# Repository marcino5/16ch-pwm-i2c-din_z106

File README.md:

# PCB 16xPWM i2c
This repository contains KiCAD files. This is an expansion module containing 16 PWM 12-24V outputs. The circuit consists of 16 N-Channel MOSFETs with a load capacity of 10A per channel controlled by a 12-bit LED controller PCA9685PW with an I2C interface. The circuit is not adapted to the maximum current, and for higher currents it is necessary to tin the exposed plus path. In my home configuration with ESPHome it works with 4 meter LED strips per channel and I did not observe any heating of the paths.

The PCB is designed to fit in a commonly available DIN rail housing.

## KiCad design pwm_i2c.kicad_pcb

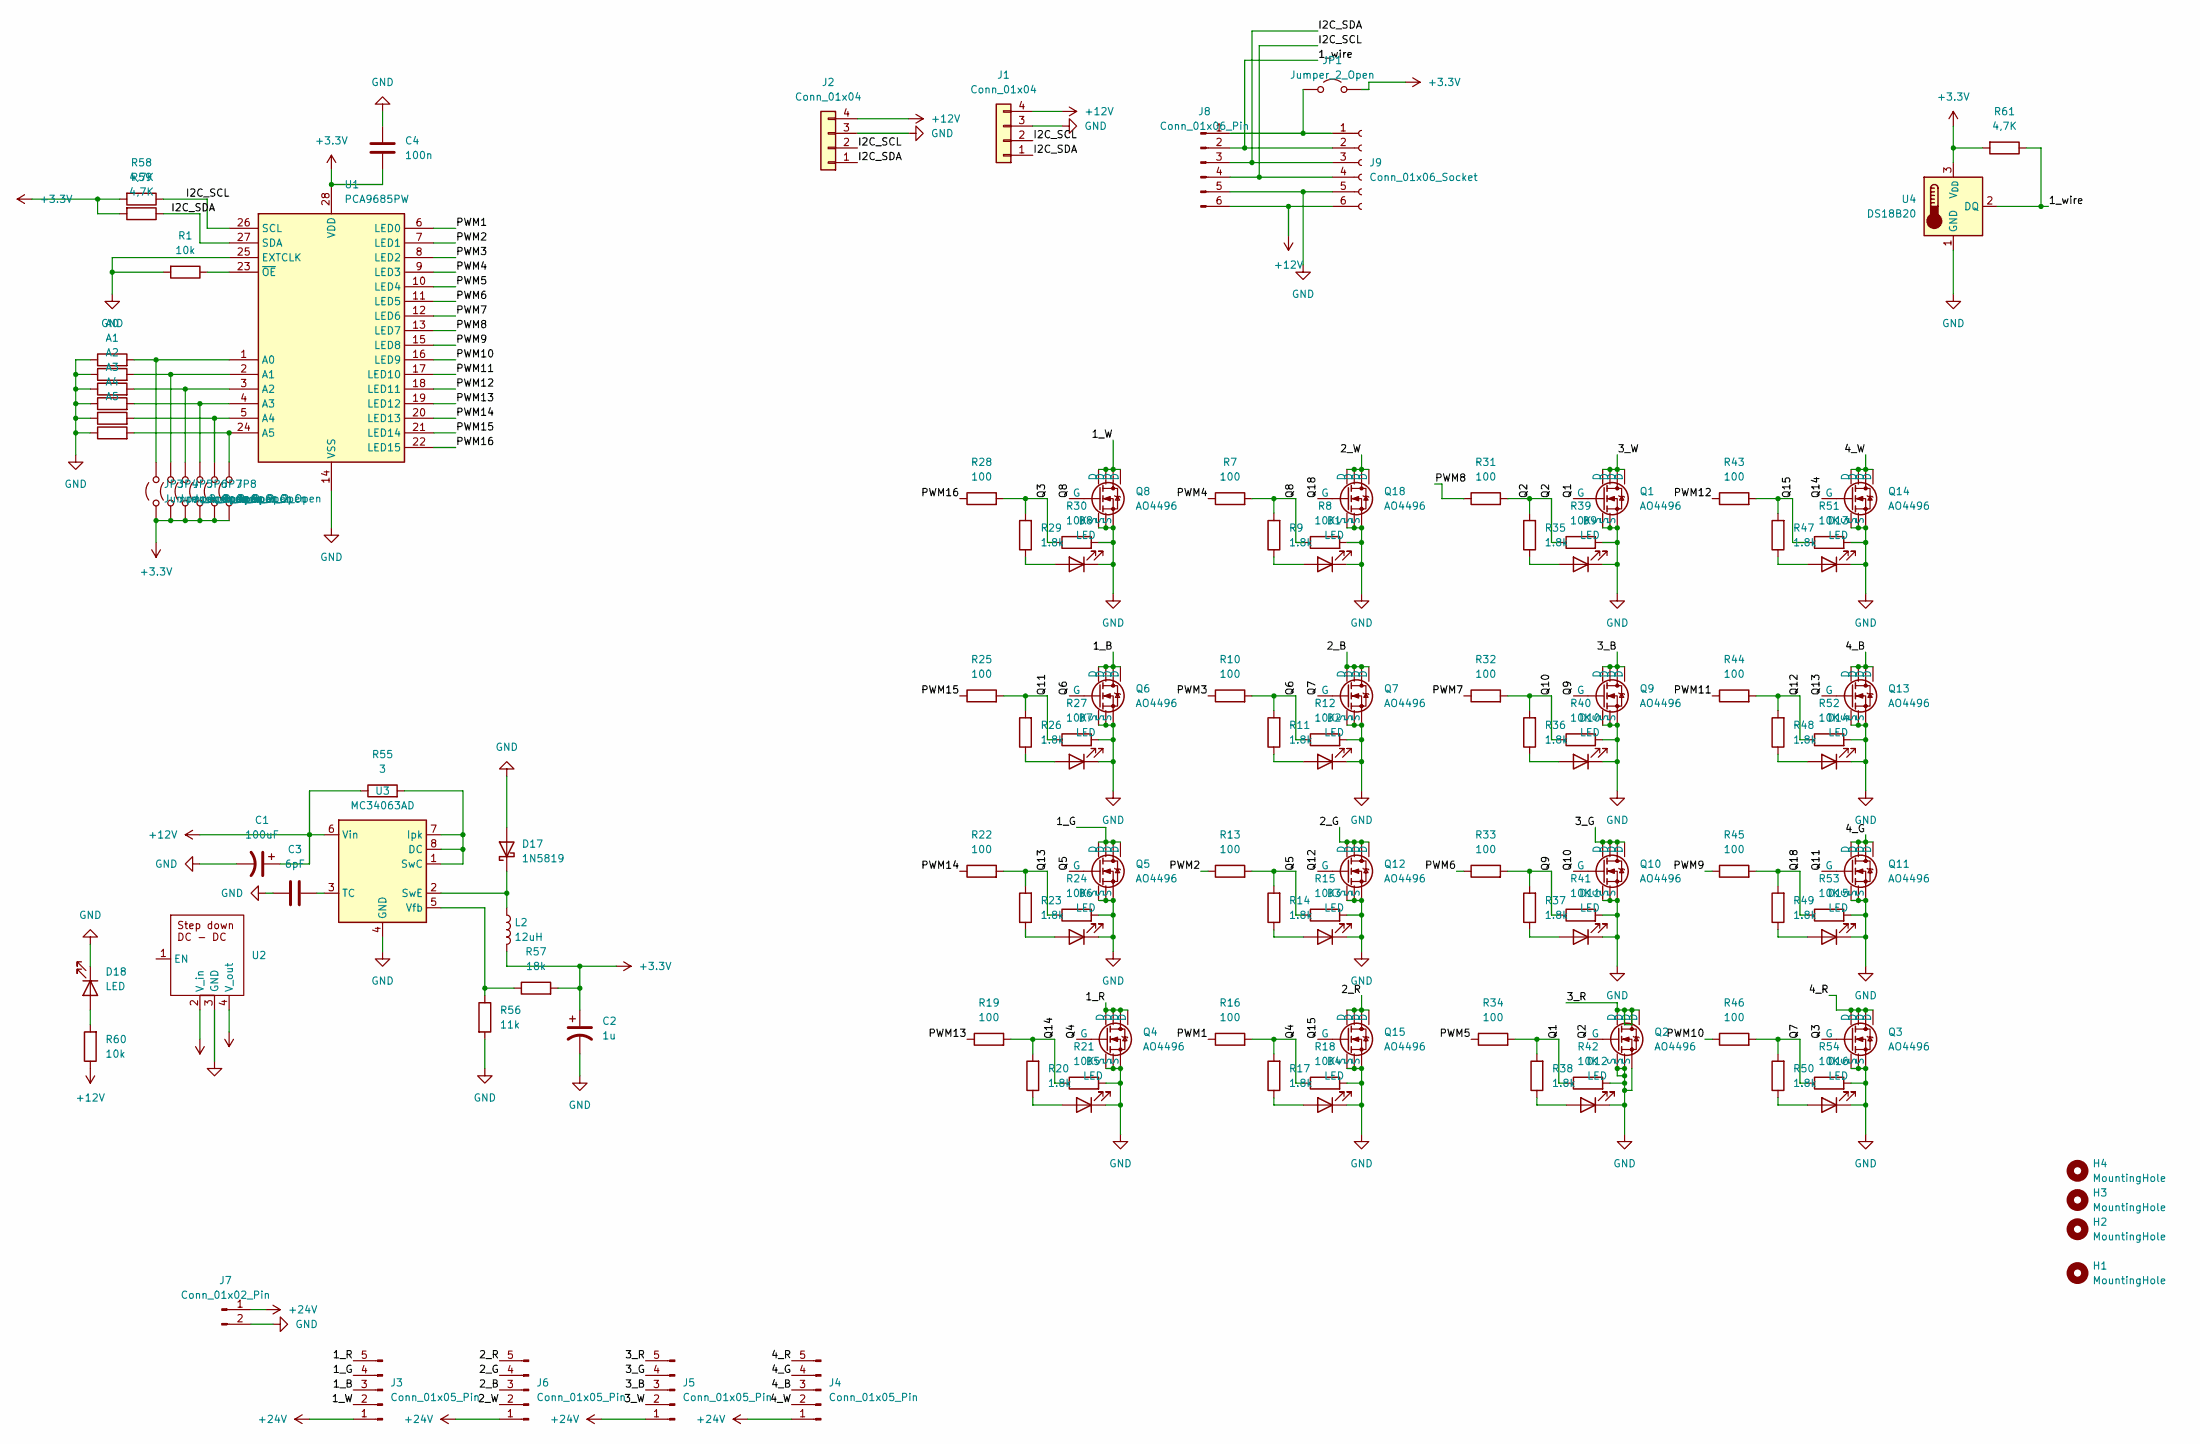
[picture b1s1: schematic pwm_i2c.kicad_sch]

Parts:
A0, A1, A2, A3, A4, A5: R_1206_3216Metric
C1: 100uF; CP_Elec_8x6.9
C2: 1u; CP_Elec_5x5.3
C3: 6pF; CP_EIA-3528-15_AVX-H
C4: 100n; C_1206_3216Metric_Pad1.33x1.80mm_HandSolder
D1, D2, D3, D4, D5, D6, D7, D8, D9, D10, D11, D12, D13, D14, D15, D16: LED; LED_1206_3216Metric
D17: 1N5819; D_MELF
D18: LED; LED_1206_3216Metric_Pad1.42x1.75mm_HandSolder
H1, H2, H3, H4: MountingHole; MountingHole_3.2mm_M3_ISO7380
J1, J2: Conn_01x04; NS-Tech_Grove_1x04_P2mm_Vertical
J3, J4, J5, J6: Conn_01x05_Pin; PhoenixContact_MC_1,5_5-G-3.81_1x05_P3.81mm_Horizontal
J7: Conn_01x02_Pin; PhoenixContact_MC_1,5_2-G-3.81_1x02_P3.81mm_Horizontal
J8: Conn_01x06_Pin; PinHeader_1x06_P2.54mm_Horizontal
J9: Conn_01x06_Socket; PinHeader_1x06_P2.54mm_Horizontal
JP1, JP3, JP4, JP5, JP6, JP7, JP8: Jumper_2_Open; SolderJumper-2_P1.3mm_Open_TrianglePad1.0x1.5mm
L2: 12uH; L_Changjiang_FNR4010S
Q1, Q2, Q3, Q4, Q5, Q6, Q7, Q8, Q9, Q10, Q11, Q12, Q13, Q14, Q15, Q18: AO4496; SO-8_5.3x6.2mm_P1.27mm
R1, R60: 10k; R_1206_3216Metric
R7, R10, R13, R16, R19, R22, R25, R28, R31, R32, R33, R34, R43, R44, R45, R46: 100; R_1206_3216Metric
R8, R12, R15, R18, R21, R24, R27, R30, R39, R40, R41, R42, R51, R52, R53, R54: 10K; R_1206_3216Metric
R9, R11, R14, R17, R20, R23, R29, R35, R36, R37, R38, R47, R48, R49, R50: 1.8k; R_1206_3216Metric
R26: 1.8k; R_1206_3216Metric_Pad1.30x1.75mm_HandSolder
R55: 3; R_1206_3216Metric
R56: 11k; R_1206_3216Metric
R57: 18k; R_1206_3216Metric
R58, R59, R61: 4,7K; R_1206_3216Metric
U1: PCA9685PW; TSSOP-28_4.4x9.7mm_P0.65mm
U2: Stocko_MKS_1654-6-0-404_1x4_P2.50mm_Vertical
U3: MC34063AD; SOIC-8_3.9x4.9mm_P1.27mm
U4: DS18B20; TO-92_Inline

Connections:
+3.3V: C2.1, C4.2, JP1.2 (B), JP3.1 (A), JP4.1 (A), JP5.1 (A), JP6.1 (A), JP7.1 (A), JP8.1 (A), L2.2, R57.2, R58.2, R59.2, R61.2, U1.28 (VDD), U2.4 (V_out), U4.3 (V_{DD})
+12V: C1.1, J1.4, J2.4, J8.6, J9.6, R55.1, R60.1, U2.2 (V_in), U3.6 (Vin)
+24V: J3.1, J4.1, J5.1, J6.1, J7.1
/1_B: J3.3, Q6.5 (D), Q6.6 (D), Q6.7 (D), Q6.8 (D)
/1_G: J3.4, Q5.5 (D), Q5.6 (D), Q5.7 (D), Q5.8 (D)
/1_R: J3.5, Q4.5 (D), Q4.6 (D), Q4.7 (D), Q4.8 (D)
/1_W: J3.2, Q8.5 (D), Q8.6 (D), Q8.7 (D), Q8.8 (D)
/1_wire: J8.2, J9.2, R61.1, U4.2 (DQ)
/2_B: J6.3, Q7.5 (D), Q7.6 (D), Q7.7 (D), Q7.8 (D)
/2_G: J6.4, Q12.5 (D), Q12.6 (D), Q12.7 (D), Q12.8 (D)
/2_R: J6.5, Q15.5 (D), Q15.6 (D), Q15.7 (D), Q15.8 (D)
/2_W: J6.2, Q18.5 (D), Q18.6 (D), Q18.7 (D), Q18.8 (D)
/3_B: J5.3, Q9.5 (D), Q9.6 (D), Q9.7 (D), Q9.8 (D)
/3_G: J5.4, Q10.5 (D), Q10.6 (D), Q10.7 (D), Q10.8 (D)
/3_R: J5.5, Q2.5 (D), Q2.6 (D), Q2.7 (D), Q2.8 (D)
/3_W: J5.2, Q1.5 (D), Q1.6 (D), Q1.7 (D), Q1.8 (D)
/4_B: J4.3, Q13.5 (D), Q13.6 (D), Q13.7 (D), Q13.8 (D)
/4_G: J4.4, Q11.5 (D), Q11.6 (D), Q11.7 (D), Q11.8 (D)
/4_R: J4.5, Q3.5 (D), Q3.6 (D), Q3.7 (D), Q3.8 (D)
/4_W: J4.2, Q14.5 (D), Q14.6 (D), Q14.7 (D), Q14.8 (D)
/I2C_SCL: J1.2, J2.2, J8.4, J9.4, R58.1, U1.26 (SCL)
/I2C_SDA: J1.1, J2.1, J8.3, J9.3, R59.1, U1.27 (SDA)
/PWM1: R16.1, U1.6 (LED0)
/PWM2: R13.1, U1.7 (LED1)
/PWM3: R10.1, U1.8 (LED2)
/PWM4: R7.1, U1.9 (LED3)
/PWM5: R34.1, U1.10 (LED4)
/PWM6: R33.1, U1.11 (LED5)
/PWM7: R32.1, U1.12 (LED6)
/PWM8: R31.1, U1.13 (LED7)
/PWM9: R45.1, U1.15 (LED8)
/PWM10: R46.1, U1.16 (LED9)
/PWM11: R44.1, U1.17 (LED10)
/PWM12: R43.1, U1.18 (LED11)
/PWM13: R19.1, U1.19 (LED12)
/PWM14: R22.1, U1.20 (LED13)
/PWM15: R25.1, U1.21 (LED14)
/PWM16: R28.1, U1.22 (LED15)
/Q1: Q1.4 (G), R34.2, R38.2, R42.1
/Q2: Q2.4 (G), R31.2, R35.2, R39.1
/Q3: Q3.4 (G), R28.2, R29.2, R30.1
/Q4: Q4.4 (G), R16.2, R17.2, R18.1
/Q5: Q5.4 (G), R13.2, R14.2, R15.1
/Q6: Q6.4 (G), R10.2, R11.2, R12.1
/Q7: Q7.4 (G), R46.2, R50.2, R54.1
/Q8: Q8.4 (G), R7.2, R8.1, R9.2
/Q9: Q9.4 (G), R33.2, R37.2, R41.1
/Q10: Q10.4 (G), R32.2, R36.2, R40.1
/Q11: Q11.4 (G), R25.2, R26.2, R27.1
/Q12: Q12.4 (G), R44.2, R48.2, R52.1
/Q13: Q13.4 (G), R22.2, R23.2, R24.1
/Q14: Q14.4 (G), R19.2, R20.2, R21.1
/Q15: Q15.4 (G), R43.2, R47.2, R51.1
/Q18: Q18.4 (G), R45.2, R49.2, R53.1
GND: A0.1, A1.1, A2.1, A3.1, A4.1, A5.1, C1.2, C2.2, C3.2, C4.1, D1.1 (K), D2.1 (K), D3.1 (K), D4.1 (K), D5.1 (K), D6.1 (K), D7.1 (K), D8.1 (K), D9.1 (K), D10.1 (K), D11.1 (K), D12.1 (K), D13.1 (K), D14.1 (K), D15.1 (K), D16.1 (K), D17.2 (A), D18.1 (K), J1.3, J2.3, J7.2, J8.5, J9.5, Q1.1 (S), Q1.2 (S), Q1.3 (S), Q2.1 (S), Q2.2 (S), Q2.3 (S), Q3.1 (S), Q3.2 (S), Q3.3 (S), Q4.1 (S), Q4.2 (S), Q4.3 (S), Q5.1 (S), Q5.2 (S), Q5.3 (S), Q6.1 (S), Q6.2 (S), Q6.3 (S), Q7.1 (S), Q7.2 (S), Q7.3 (S), Q8.1 (S), Q8.2 (S), Q8.3 (S), Q9.1 (S), Q9.2 (S), Q9.3 (S), Q10.1 (S), Q10.2 (S), Q10.3 (S), Q11.1 (S), Q11.2 (S), Q11.3 (S), Q12.1 (S), Q12.2 (S), Q12.3 (S), Q13.1 (S), Q13.2 (S), Q13.3 (S), Q14.1 (S), Q14.2 (S), Q14.3 (S), Q15.1 (S), Q15.2 (S), Q15.3 (S), Q18.1 (S), Q18.2 (S), Q18.3 (S), R1.2, R8.2, R12.2, R15.2, R18.2, R21.2, R24.2, R27.2, R30.2, R39.2, R40.2, R41.2, R42.2, R51.2, R52.2, R53.2, R54.2, R56.2, U1.14 (VSS), U1.25 (EXTCLK), U2.3 (GND), U3.4 (GND), U4.1 (GND)
unnamed: D1.2 (A), R9.1
unnamed: D2.2 (A), R11.1
unnamed: D3.2 (A), R14.1
unnamed: D4.2 (A), R17.1
unnamed: D5.2 (A), R20.1
unnamed: D6.2 (A), R23.1
unnamed: D7.2 (A), R26.1
unnamed: D8.2 (A), R29.1
unnamed: D9.2 (A), R35.1
unnamed: D10.2 (A), R36.1
unnamed: D11.2 (A), R37.1
unnamed: D12.2 (A), R38.1
unnamed: D13.2 (A), R47.1
unnamed: D14.2 (A), R48.1
unnamed: D15.2 (A), R49.1
unnamed: D16.2 (A), R50.1
unnamed: D17.1 (K), L2.1, U3.2 (SwE)
unnamed: D18.2 (A), R60.2
unnamed: J8.1, J9.1, JP1.1 (A)
unnamed: A0.2, JP3.2 (B), U1.1 (A0)
unnamed: A1.2, JP4.2 (B), U1.2 (A1)
unnamed: A2.2, JP5.2 (B), U1.3 (A2)
unnamed: A3.2, JP6.2 (B), U1.4 (A3)
unnamed: A4.2, JP7.2 (B), U1.5 (A4)
unnamed: A5.2, JP8.2 (B), U1.24 (A5)
unnamed: R1.1, U1.23 (~OE)
unnamed: R55.2, U3.1 (SwC), U3.7 (Ipk), U3.8 (DC)
unnamed: C3.1, U3.3 (TC)
unnamed: R56.1, R57.1, U3.5 (Vfb)

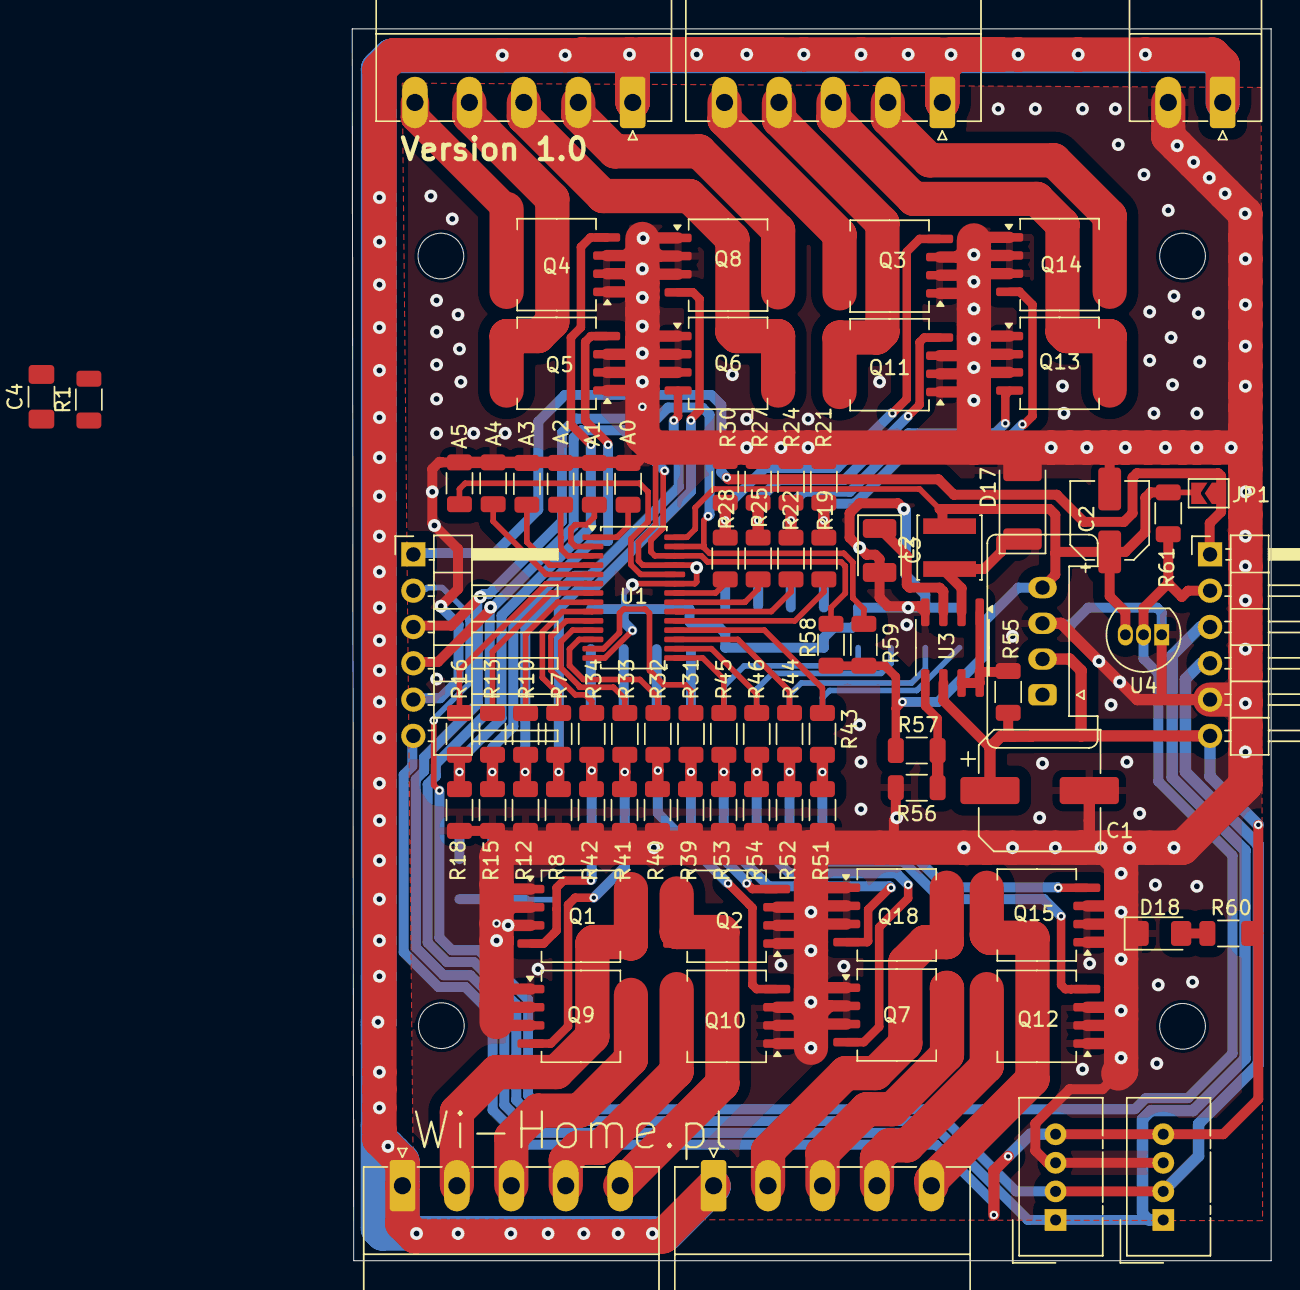
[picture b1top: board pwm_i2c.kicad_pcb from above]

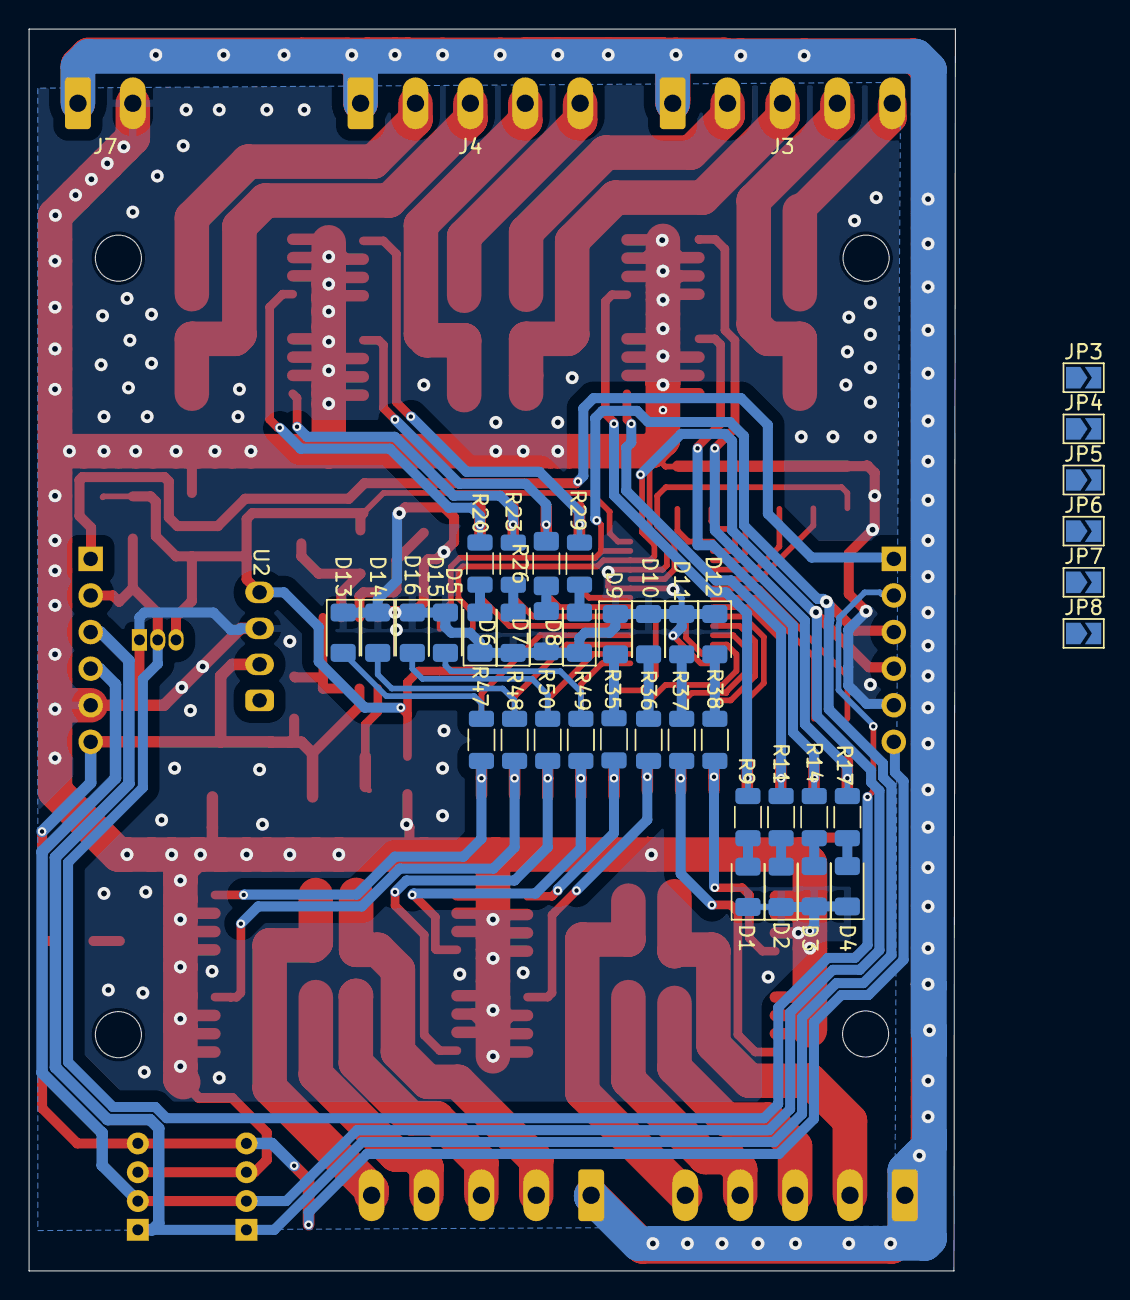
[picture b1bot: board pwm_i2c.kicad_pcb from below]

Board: 4 copper layers, 64.3 x 86.2 mm, 125 parts (38 on the bottom side), 84 nets.

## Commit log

2025-01-28 first version
2025-01-28 documentation
2025-01-28 Update README.md
    update readme
